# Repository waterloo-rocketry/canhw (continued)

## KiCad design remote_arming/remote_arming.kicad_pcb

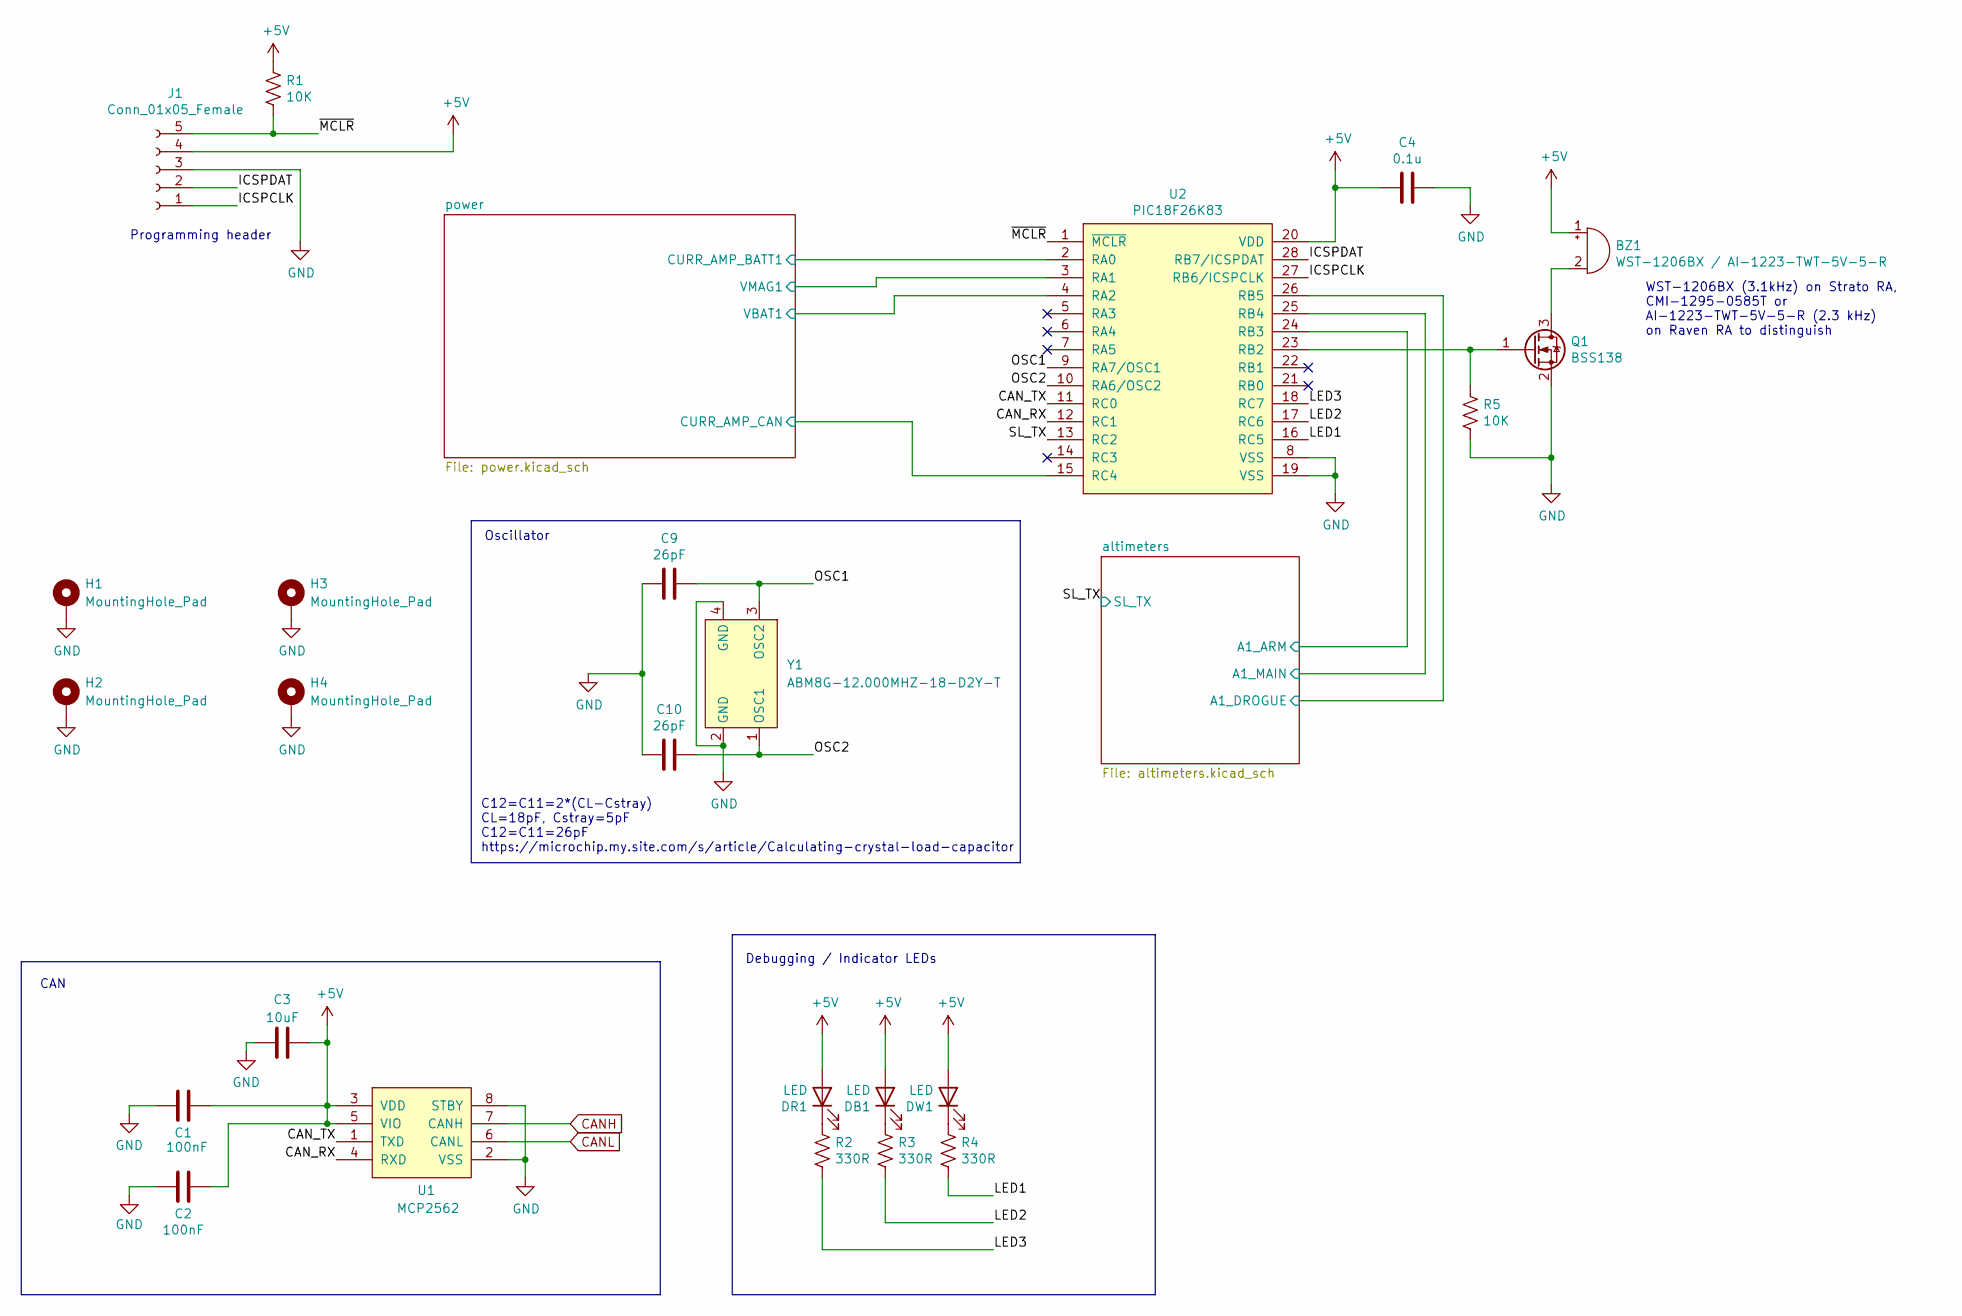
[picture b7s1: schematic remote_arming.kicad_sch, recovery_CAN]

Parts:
BZ1: WST-1206BX / AI-1223-TWT-5V-5-R; Buzzer_12x9.5RM7.6
C1, C2: 100nF; C_0603_1608Metric_Pad1.08x0.95mm_HandSolder
C3: 10uF; C_0603_1608Metric_Pad1.08x0.95mm_HandSolder
C4: 0.1u; C_0603_1608Metric_Pad1.08x0.95mm_HandSolder
C9: 26pF; C_0603_1608Metric
C10: 26pF; C_0603_1608Metric_Pad1.08x0.95mm_HandSolder
DB1: LED; LED_1206_3216Metric_Pad1.42x1.75mm_HandSolder
DR1: LED; LED_1206_3216Metric_Pad1.42x1.75mm_HandSolder
DW1: LED; LED_1206_3216Metric_Pad1.42x1.75mm_HandSolder
H1, H2, H3, H4: MountingHole_Pad; MountingHole_3.2mm_M3_Pad_TopBottom
J1: Conn_01x05_Female; PinSocket_5x2.54_SMD_90deg_952-3198-1-ND
Q1: BSS138; SOT-23_Handsoldering
R1, R5: 10K; R_0603_1608Metric_Pad0.98x0.95mm_HandSolder
R2, R3, R4: 330R; R_0603_1608Metric_Pad0.98x0.95mm_HandSolder
U1: MCP2562; SOIC-8_3.9x4.9mm_P1.27mm
U2: PIC18F26K83; SOIC-28W_7.5x18.7mm_P1.27mm
Y1: ABM8G-12.000MHZ-18-D2Y-T; Crystal_SMD_Abracon_ABM8G-4Pin_3.2x2.5mm

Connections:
+5V: BZ1.1 (-), C1.2, C2.1, C3.2, C4.2, DB1.2 (A), DR1.2 (A), DW1.2 (A), J1.4, R1.1, U1.3 (VDD), U1.5 (VIO), U2.20 (VDD); also elsewhere on the board
/CAN_RX: U1.4 (RXD), U2.12 (RC1)
/CAN_TX: U1.1 (TXD), U2.11 (RC0)
/ICSPCLK: J1.1, U2.27 (RB6/ICSPCLK)
/ICSPDAT: J1.2, U2.28 (RB7/ICSPDAT)
/LED1: R4.2, U2.16 (RC5)
/LED2: R3.2, U2.17 (RC6)
/LED3: R2.2, U2.18 (RC7)
/OSC1: C9.1, U2.9 (RA7/OSC1), Y1.3 (OSC2)
/OSC2: C10.1, U2.10 (RA6/OSC2), Y1.1 (OSC1)
/SL_TX: U2.13 (RC2); also elsewhere on the board
/altimeters/A1_ARM: U2.24 (RB3); also elsewhere on the board
/altimeters/A1_DROGUE: U2.26 (RB5); also elsewhere on the board
/altimeters/A1_MAIN: U2.25 (RB4); also elsewhere on the board
/power/CURR_AMP_BATT1: U2.2 (RA0); also elsewhere on the board
/power/CURR_AMP_CAN: U2.15 (RC4); also elsewhere on the board
/power/VBAT1: U2.4 (RA2); also elsewhere on the board
/power/VMAG1: U2.3 (RA1); also elsewhere on the board
/~MCLR: J1.5, R1.2, U2.1 (~MCLR)
CANH: U1.7 (CANH); also elsewhere on the board
CANL: U1.6 (CANL); also elsewhere on the board
GND: C1.1, C2.2, C3.1, C4.1, C9.2, C10.2, H1.1, H2.1, H3.1, H4.1, J1.3, Q1.2 (S), R5.2, U1.2 (VSS), U1.8 (STBY), U2.8 (VSS), U2.19 (VSS), Y1.2 (GND), Y1.4 (GND); also elsewhere on the board
unnamed: BZ1.2 (+), Q1.3 (D)
unnamed: DB1.1 (K), R3.1
unnamed: DR1.1 (K), R2.1
unnamed: DW1.1 (K), R4.1
unnamed: Q1.1 (G), R5.1, U2.23 (RB2)

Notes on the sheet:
Oscillator
Debugging / Indicator LEDs
WST-1206BX (3.1kHz) on Strato RA, CMI-1295-0585T or AI-1223-TWT-5V-5-R (2.3 kHz) on Raven RA to distinguish
C12=C11=2*(CL-Cstray) CL=18pF, Cstray=5pF C12=C11=26pF https://microchip.my.site.com/s/article/Calculating-crystal-load-capacitor
CAN
Programming header

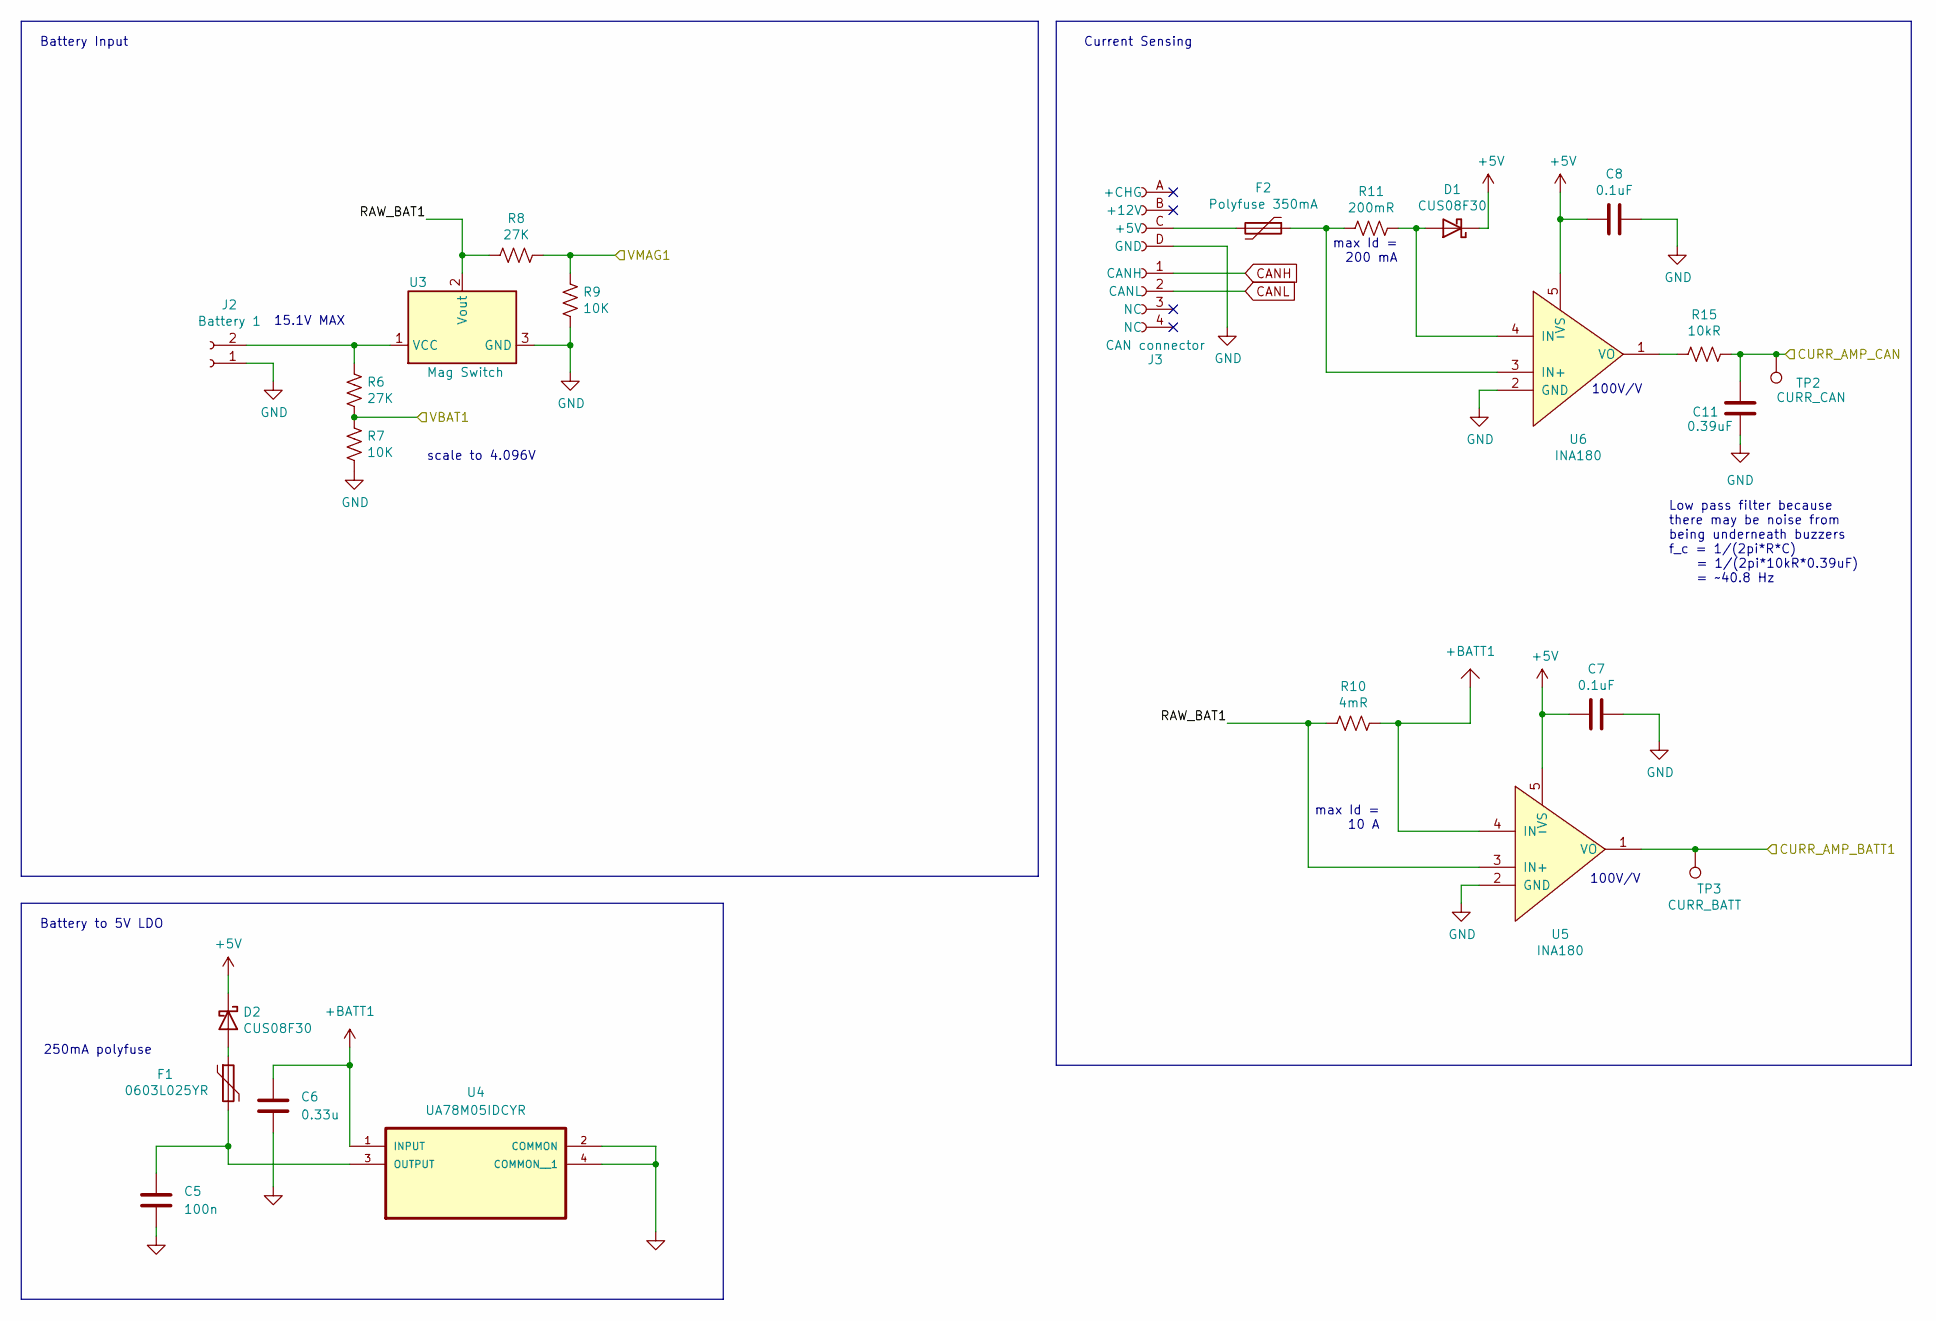
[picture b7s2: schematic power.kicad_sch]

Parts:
C5: 100n; C_0603_1608Metric_Pad1.08x0.95mm_HandSolder
C6: 0.33u; C_0603_1608Metric_Pad1.08x0.95mm_HandSolder
C7, C8: 0.1uF; C_0603_1608Metric_Pad1.08x0.95mm_HandSolder
C11: 0.39uF; C_0603_1608Metric_Pad1.08x0.95mm_HandSolder
D1, D2: CUS08F30; D_SOD-323_HandSoldering
F1: 0603L025YR; Fuse_0603_1608Metric_Pad1.05x0.95mm_HandSolder
F2: Polyfuse 350mA; Fuse_1206_3216Metric_Pad1.42x1.75mm_HandSolder
J2: Battery 1; BarrierBlock_ED2945-ND
J3: CAN connector; connector_Harwin_G125-MH104M4-04AD000P
R6, R8: 27K; R_0603_1608Metric_Pad0.98x0.95mm_HandSolder
R7, R9: 10K; R_0603_1608Metric_Pad0.98x0.95mm_HandSolder
R10: 4mR; R_1206_3216Metric_Pad1.30x1.75mm_HandSolder
R11: 200mR; R_0603_1608Metric_Pad0.98x0.95mm_HandSolder
R15: 10kR; R_0603_1608Metric_Pad0.98x0.95mm_HandSolder
TP2: CURR_CAN; TestPoint_Pad_D2.0mm
TP3: CURR_BATT; TestPoint_Pad_D2.0mm
U3: Mag Switch
U4: UA78M05IDCYR; SOT230P700X180-4N
U5, U6: INA180; SOT-23-5_HandSoldering

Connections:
+5V: C7.2, C8.2, D1.1 (K), D2.1 (K), U5.5 (VS), U6.5 (VS); also elsewhere on the board
+BATT1: C6.1, R10.1, U4.1 (INPUT), U5.4 (IN-); also elsewhere on the board
/power/CURR_AMP_BATT1: TP3.1, U5.1 (VO); also elsewhere on the board
/power/CURR_AMP_CAN: C11.1, R15.2, TP2.1; also elsewhere on the board
/power/RAW_BAT1: R8.2, R10.2, U3.2 (Vout), U5.3 (IN+)
/power/VBAT1: R6.2, R7.1; also elsewhere on the board
/power/VMAG1: R8.1, R9.1; also elsewhere on the board
CANH: J3.1 (CANH); also elsewhere on the board
CANL: J3.2 (CANL); also elsewhere on the board
GND: C5.2, C6.2, C7.1, C8.1, C11.2, J2.1, J3.D (GND), R7.2, R9.2, U3.3 (GND), U4.2 (COMMON), U4.4 (COMMON__1), U5.2 (GND), U6.2 (GND); also elsewhere on the board
unnamed: D1.2 (A), R11.1, U6.4 (IN-)
unnamed: D2.2 (A), F1.1
unnamed: J2.2, R6.1, U3.1 (VCC)
unnamed: F2.2, J3.C (+5V)
unnamed: C5.1, F1.2, U4.3 (OUTPUT)
unnamed: F2.1, R11.2, U6.3 (IN+)
unnamed: R15.1, U6.1 (VO)

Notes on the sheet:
100V/V
max Id = 200 mA
max Id = 10 A
Battery Input
250mA polyfuse
Current Sensing
Battery to 5V LDO
scale to 4.096V
Low pass filter because there may be noise from being underneath buzzers f_c = 1/(2pi*R*C) = 1/(2pi*10kR*0.39uF) = ~40.8 Hz
15.1V MAX

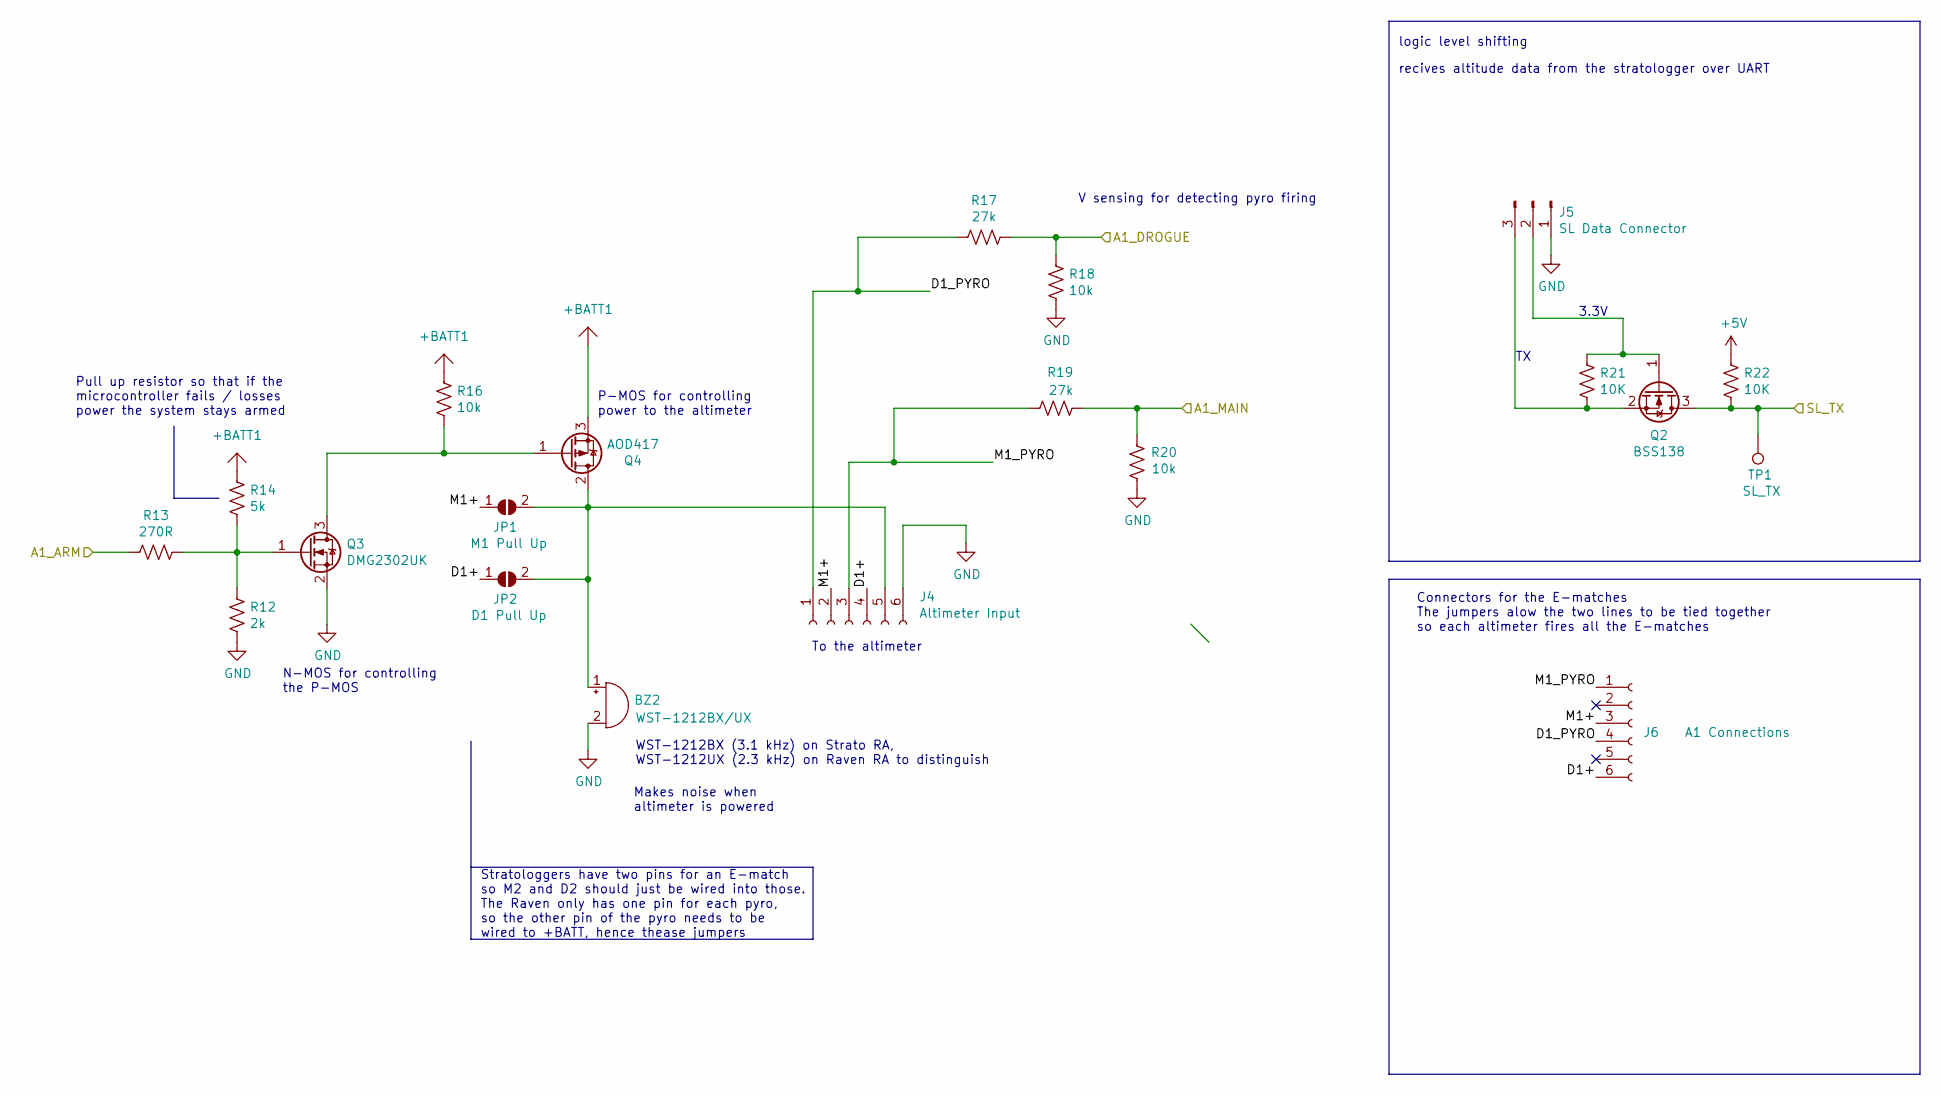
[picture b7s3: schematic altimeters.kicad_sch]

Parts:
BZ2: WST-1212BX/UX; Buzzer_12x9.5RM7.6
J4: Altimeter Input; connector_Harwin_G125–MG10605M4P
J5: SL Data Connector; JST_EH_S3B-EH_1x03_P2.50mm_Horizontal
J6: A1 Connections; connector_Harwin_G125–MG10605M4P
JP1: M1 Pull Up; SolderJumper-2_P1.3mm_Open_RoundedPad1.0x1.5mm
JP2: D1 Pull Up; SolderJumper-2_P1.3mm_Open_RoundedPad1.0x1.5mm
Q2: BSS138; SOT-23_Handsoldering
Q3: DMG2302UK; SOT-23_Handsoldering
Q4: AOD417; TO-252-2
R12: 2k; R_0603_1608Metric_Pad0.98x0.95mm_HandSolder
R13: 270R; R_0603_1608Metric_Pad0.98x0.95mm_HandSolder
R14: 5k; R_0603_1608Metric_Pad0.98x0.95mm_HandSolder
R16, R18, R20: 10k; R_0603_1608Metric_Pad0.98x0.95mm_HandSolder
R17, R19: 27k; R_0603_1608Metric_Pad0.98x0.95mm_HandSolder
R21, R22: 10K; R_0603_1608Metric_Pad0.98x0.95mm_HandSolder
TP1: SL_TX; TestPoint_Pad_D2.0mm

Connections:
+5V: R22.1; also elsewhere on the board
+BATT1: Q4.3 (S), R14.1, R16.1; also elsewhere on the board
/SL_TX: Q2.3 (D), R22.2, TP1.1; also elsewhere on the board
/altimeters/A1_ARM: R13.2; also elsewhere on the board
/altimeters/A1_DROGUE: R17.1, R18.2; also elsewhere on the board
/altimeters/A1_MAIN: R19.2, R20.2; also elsewhere on the board
/altimeters/D1+: J4.4, J6.6, JP2.1 (A)
/altimeters/D1_PYRO: J4.1, J6.4, R17.2
/altimeters/M1+: J4.2, J6.3, JP1.1 (A)
/altimeters/M1_PYRO: J4.3, J6.1, R19.1
GND: BZ2.2 (+), J4.6, J5.1, Q3.2 (S), R12.2, R18.1, R20.1; also elsewhere on the board
unnamed: BZ2.1 (-), J4.5, JP1.2 (B), JP2.2 (B), Q4.2 (D)
unnamed: J5.2, Q2.1 (G), R21.1
unnamed: J5.3, Q2.2 (S), R21.2
unnamed: Q3.3 (D), Q4.1 (G), R16.2
unnamed: Q3.1 (G), R12.1, R13.1, R14.2

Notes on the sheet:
To the altimeter
N-MOS for controlling the P-MOS
logic level shifting
WST-1212BX (3.1 kHz) on Strato RA, WST-1212UX (2.3 kHz) on Raven RA to distinguish
P-MOS for controlling power to the altimeter
3.3V
recives altitude data from the stratologger over UART
Pull up resistor so that if the microcontroller fails / losses power the system stays armed
Stratologgers have two pins for an E-match so M2 and D2 should just be wired into those. The Raven only has one pin for each pyro, so the other pin of the pyro needs to be wired to +BATT, hence thease jumpers
V sensing for detecting pyro firing
Connectors for the E-matches The jumpers alow the two lines to be tied together so each altimeter fires all the E-matches
Makes noise when altimeter is powered

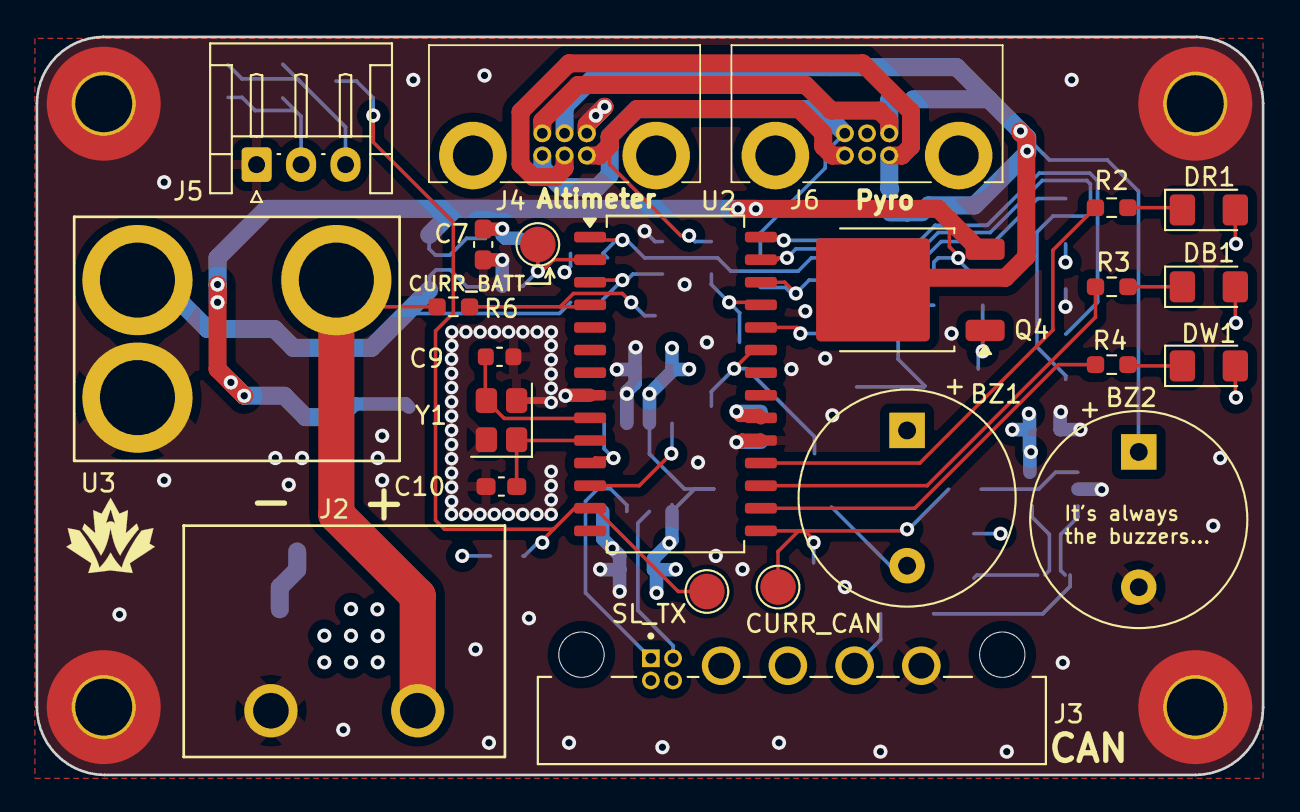
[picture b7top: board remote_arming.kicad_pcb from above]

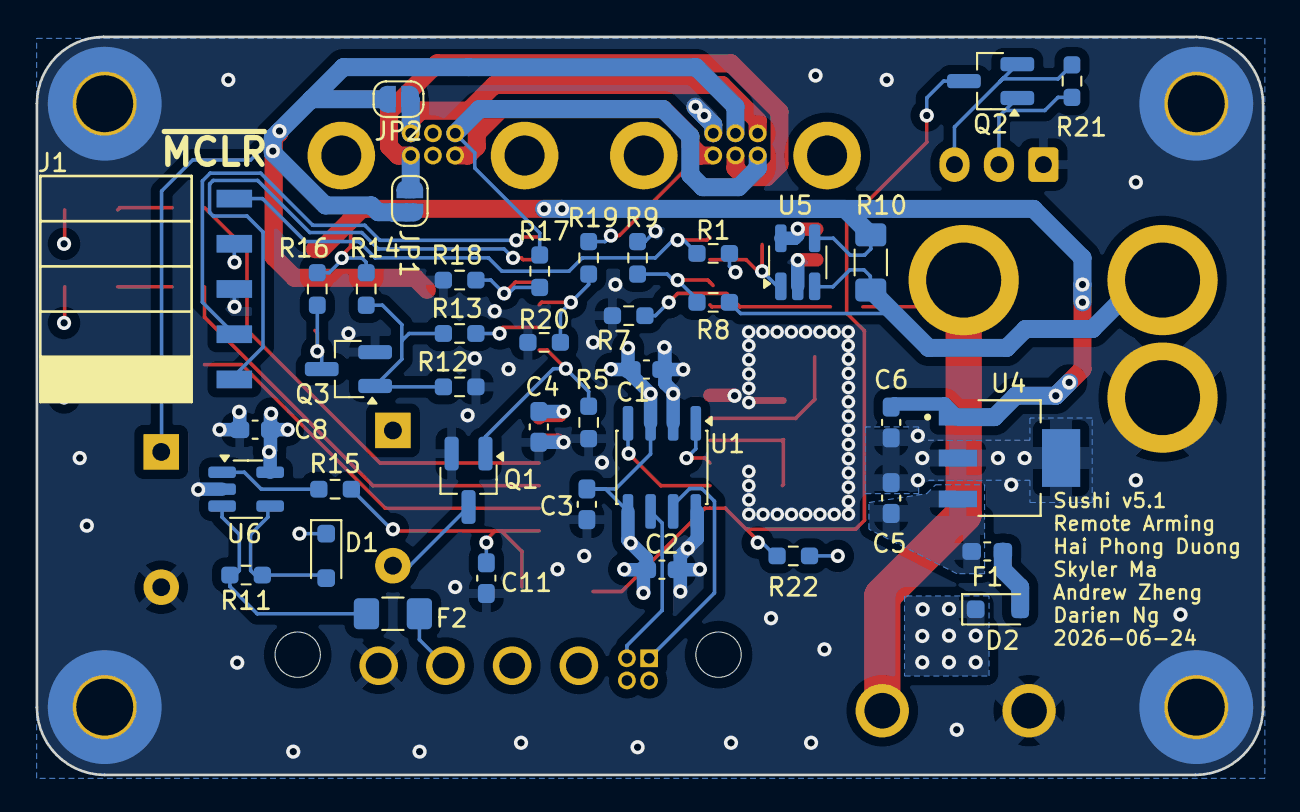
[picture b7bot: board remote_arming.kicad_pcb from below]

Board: 4 copper layers, 68.9 x 41.5 mm, 68 parts (40 on the bottom side), 45 nets.

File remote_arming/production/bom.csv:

Designator,Footprint,Quantity,Value,LCSC Part #
BZ1,Buzzer_12x9.5RM7.6,1,CMI-1295-0585T,
BZ2,Buzzer_12x9.5RM7.6,1,CMI-1295-1285T,
"C1, C2",0603,2,100nF,
"C10, C9",0603,2,26pF,
C11,0603,1,0.39uF,
C3,0603,1,10uF,
C4,0603,1,0.1u,
C5,0603,1,100n,
C6,0603,1,0.33u,
"C7, C8",0603,2,0.1uF,
"D1, D2",D_SOD-323_HandSoldering,2,CUS08F30,
"DB1, DR1, DW1",1206,3,LED,
F1,0603,1,0603L025YR,
F2,1206,1,Polyfuse 350mA,
J1,PinSocket_5x2.54_SMD_90deg_952-3198-1-ND,1,Conn_01x05_Female,
J2,BarrierBlock_ED2945-ND,1,Battery 1,
J3,connector_Harwin_G125-MH104M4-04AD000P,1,CAN connector,
J4,connector_Harwin_G125–MG10605M4P,1,Altimeter Input,
J5,JST_EH_S3B-EH_1x03_P2.50mm_Horizontal,1,SL Data Connector,
J6,connector_Harwin_G125–MG10605M4P,1,A1 Connections,
JP1,SolderJumper-2_P1.3mm_Open_RoundedPad1.0x1.5mm,1,M1 Pull Up,
JP2,SolderJumper-2_P1.3mm_Open_RoundedPad1.0x1.5mm,1,D1 Pull Up,
"Q1, Q2",SOT-23_Handsoldering,2,BSS138,
Q3,SOT-23_Handsoldering,1,DMG2302UK,
Q4,TO-252-2,1,AOD417,
"R1, R16, R18, R20, R21, R22, R5, R7, R9",0603,9,10K,
R10,1206,1,4mR,
R11,0603,1,200mR,
R12,0603,1,2k,
R13,0603,1,270R,
R14,0603,1,5k,
R15,0603,1,10kR,
"R17, R19, R6, R8",0603,4,27k,
"R2, R3, R4",0603,3,330R,
TP1,TestPoint_Pad_D2.0mm,1,SL_TX,
TP2,TestPoint_Pad_D2.0mm,1,CURR_CAN,
TP3,TestPoint_Pad_D2.0mm,1,CURR_BATT,
U1,SOIC-8_3.9x4.9mm_P1.27mm,1,MCP2562,
U2,SOIC-28W_7.5x18.7mm_P1.27mm,1,PIC18F26K83,
U3,Mag Switch,1,Mag Switch,
U4,SOT230P700X180-4N,1,UA78M05IDCYR,
"U5, U6",SOT-23-5_HandSoldering,2,INA180,
Y1,Crystal_SMD_Abracon_ABM8G-4Pin_3.2x2.5mm,1,ABM8G-12.000MHZ-18-D2Y-T,

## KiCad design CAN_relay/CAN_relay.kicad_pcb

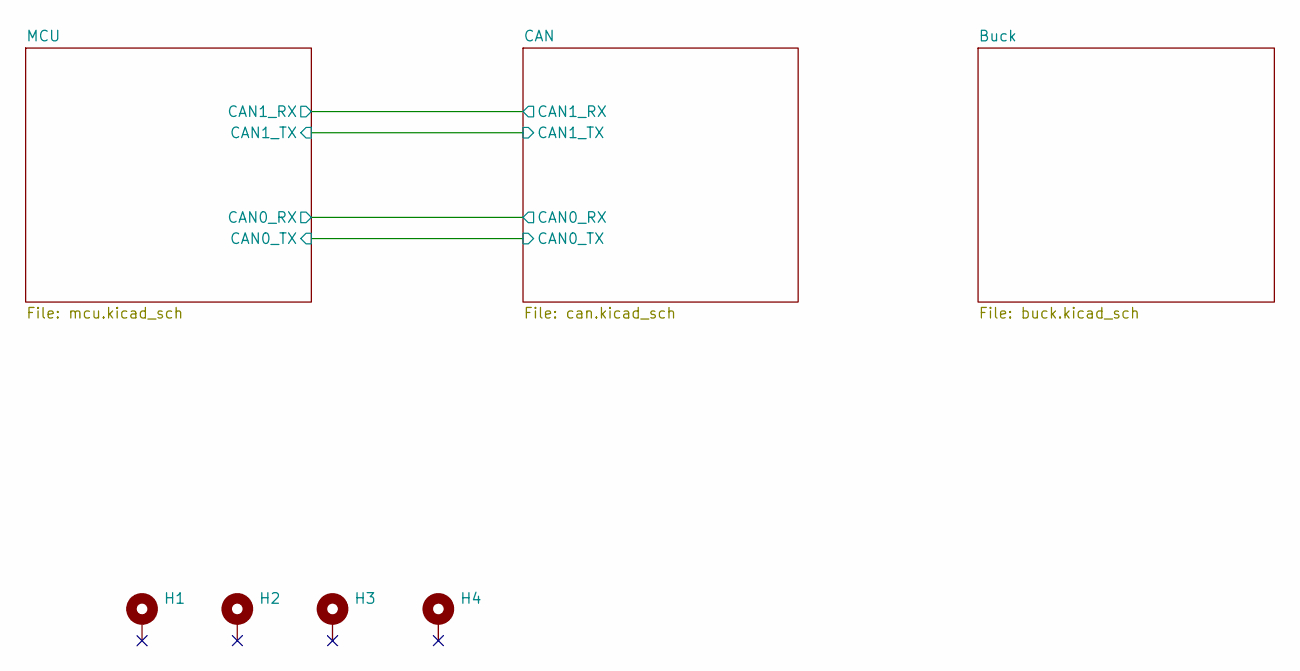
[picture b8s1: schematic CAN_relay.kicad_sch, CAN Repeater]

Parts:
H1, H2, H3, H4: MountingHole_Pad; MountingHole_3.2mm_M3_Pad

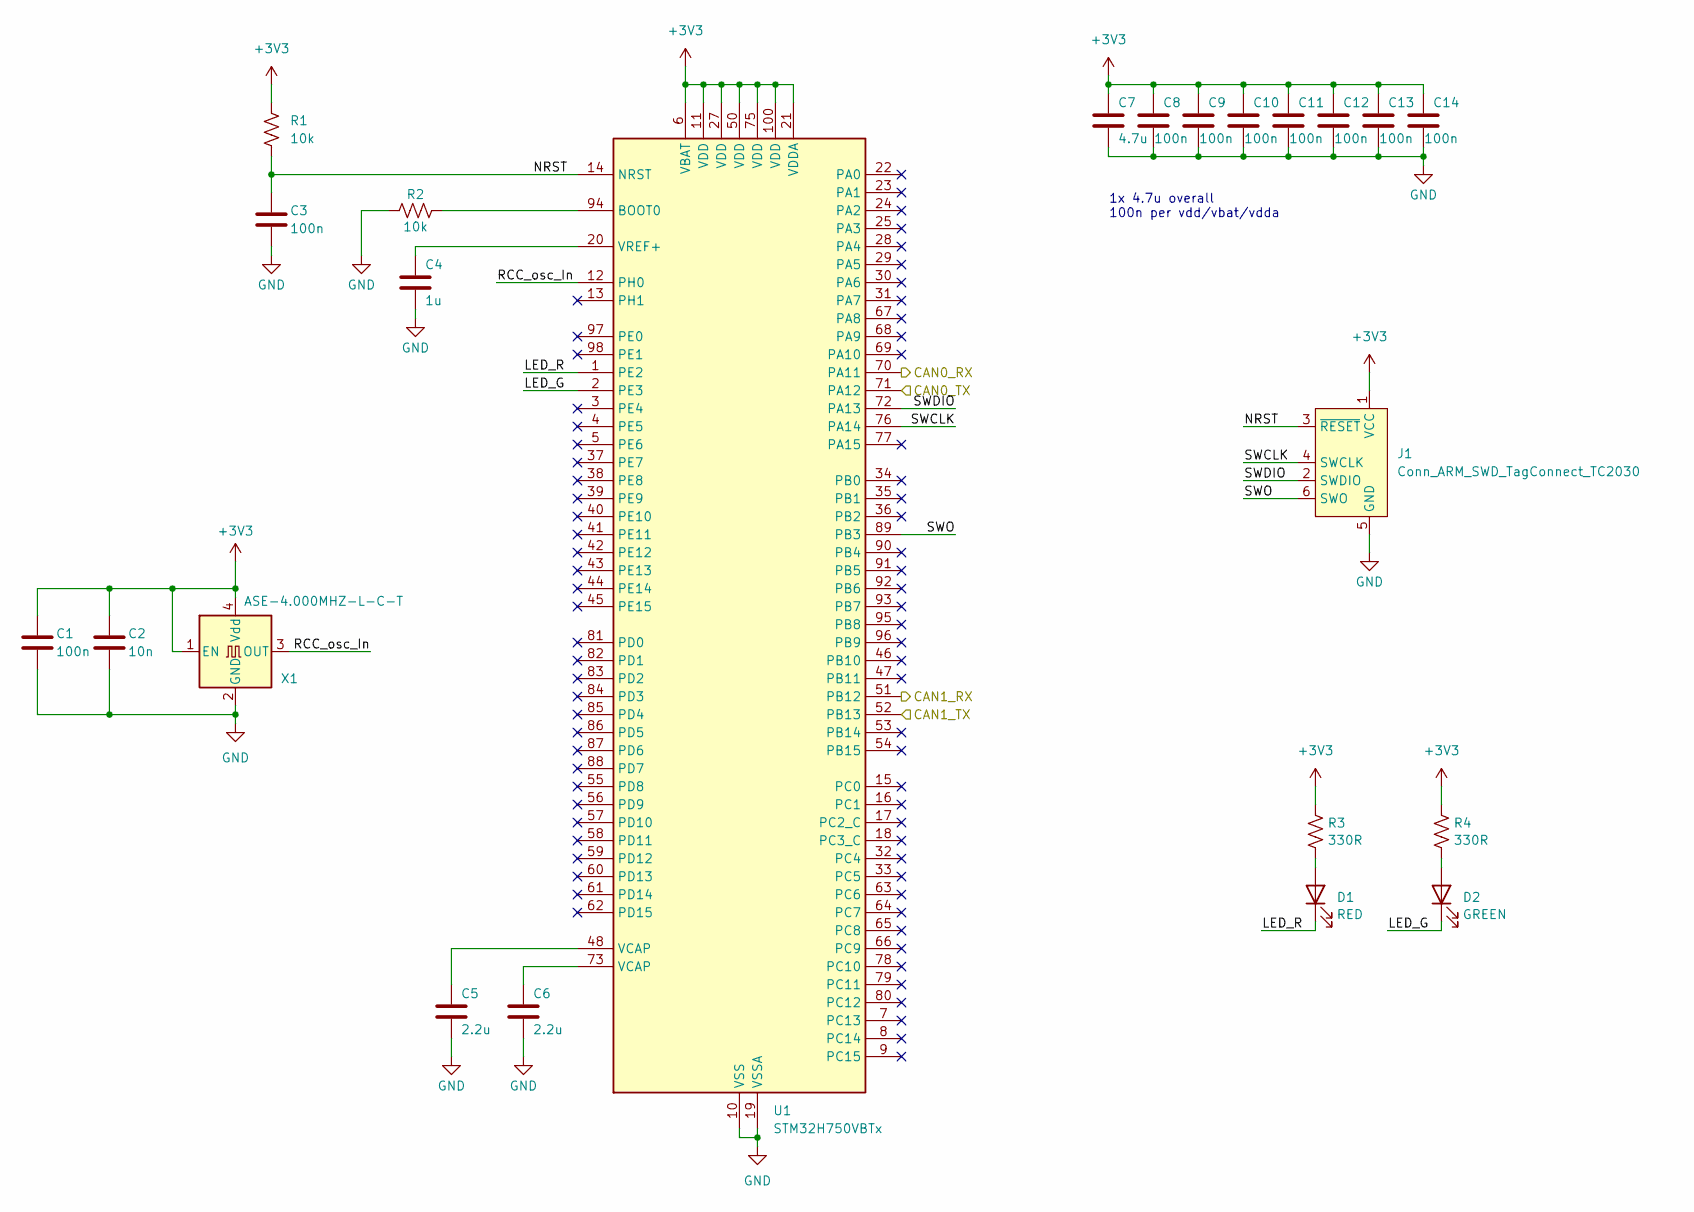
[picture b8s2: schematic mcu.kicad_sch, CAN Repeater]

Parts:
C1, C3, C8, C9, C10, C11, C12, C13, C14: 100n; C_0603_1608Metric_Pad1.08x0.95mm_HandSolder
C2: 10n; C_0603_1608Metric_Pad1.08x0.95mm_HandSolder
C4: 1u; C_0603_1608Metric_Pad1.08x0.95mm_HandSolder
C5, C6: 2.2u; C_0603_1608Metric_Pad1.08x0.95mm_HandSolder
C7: 4.7u; C_0603_1608Metric_Pad1.08x0.95mm_HandSolder
D1: RED; LED_1206_3216Metric_Pad1.42x1.75mm_HandSolder
D2: GREEN; LED_1206_3216Metric_Pad1.42x1.75mm_HandSolder
J1: Conn_ARM_SWD_TagConnect_TC2030; Tag-Connect_TC2030-IDC-FP_2x03_P1.27mm_Vertical
R1, R2: 10k; R_0603_1608Metric_Pad0.98x0.95mm_HandSolder
R3, R4: 330R; R_0603_1608Metric_Pad0.98x0.95mm_HandSolder
U1: STM32H750VBTx; LQFP-100_14x14mm_P0.5mm
X1: ASE-4.000MHZ-L-C-T; Oscillator_SMD_Abracon_ASE-4Pin_3.2x2.5mm; LCSC Part # C437121

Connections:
+3V3: C1.1, C2.1, C7.1, C8.1, C9.1, C10.1, C11.1, C12.1, C13.1, C14.1, J1.1 (VCC), R1.1, R3.1, R4.1, U1.6 (VBAT), U1.11 (VDD), U1.21 (VDDA), U1.27 (VDD), U1.50 (VDD), U1.75 (VDD), U1.100 (VDD), X1.1 (EN), X1.4 (Vdd); also elsewhere on the board
/CAN/CAN0_RX: U1.70 (PA11); also elsewhere on the board
/CAN/CAN0_TX: U1.71 (PA12); also elsewhere on the board
/CAN/CAN1_RX: U1.51 (PB12); also elsewhere on the board
/CAN/CAN1_TX: U1.52 (PB13); also elsewhere on the board
/MCU/LED_G: D2.1 (K), U1.2 (PE3)
/MCU/LED_R: D1.1 (K), U1.1 (PE2)
/MCU/NRST: C3.1, J1.3 (~RESET), R1.2, U1.14 (NRST)
/MCU/RCC_osc_In: U1.12 (PH0), X1.3 (OUT)
/MCU/SWCLK: J1.4 (SWCLK), U1.76 (PA14)
/MCU/SWDIO: J1.2 (SWDIO), U1.72 (PA13)
/MCU/SWO: J1.6 (SWO), U1.89 (PB3)
GND: C1.2, C2.2, C3.2, C4.2, C5.2, C6.2, C7.2, C8.2, C9.2, C10.2, C11.2, C12.2, C13.2, C14.2, J1.5 (GND), R2.1, U1.10 (VSS), U1.19 (VSSA), U1.26 (VSS), U1.49 (VSS), U1.74 (VSS), U1.99 (VSS), X1.2 (GND); also elsewhere on the board
unnamed: C5.1, U1.48 (VCAP)
unnamed: C6.1, U1.73 (VCAP)
unnamed: D1.2 (A), R3.2
unnamed: D2.2 (A), R4.2
unnamed: R2.2, U1.94 (BOOT0)
unnamed: C4.1, U1.20 (VREF+)

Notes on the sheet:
1x 4.7u overall 100n per vdd/vbat/vdda

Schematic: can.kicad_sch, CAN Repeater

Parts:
C16, C17, C18, C19: 100n; C_0603_1608Metric_Pad1.08x0.95mm_HandSolder
D3, D4: PMEG2010ER; Nexperia_CFP3_SOD-123W
D5, D6: ESDCAN01-2BLY; SOT-23; LCSC Part # C1976606
F1: PTC 250mA; Fuse_1206_3216Metric_Pad1.42x1.75mm_HandSolder
J2, J3: G125-MH104M4-04AD000P; connector_Harwin_G125-MH104M4-04AD000P
JP1, JP2: SolderJumper_2_Open; SolderJumper-2_P1.3mm_Open_RoundedPad1.0x1.5mm
R5, R6: 120R; R_0603_1608Metric_Pad0.98x0.95mm_HandSolder; not fitted
TP1, TP3: RCAN_TX; TestPoint_Pad_D1.0mm
TP2, TP4: RCAN_RX; TestPoint_Pad_D1.0mm
U2, U3: TCAN3413DDFR; Manufacturer_Part_Number TCAN3413DDFR

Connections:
+3V3: C16.1, C17.1, C18.1, C19.1, U2.3 (VCC), U2.5 (VIO), U3.3 (VCC), U3.5 (VIO); also elsewhere on the board
+VIN: F1.2; also elsewhere on the board
/CAN/CAN0_H: D6.1 (K), J2.1 (CANH), JP1.2 (B), R6.2, U3.7 (CANH)
/CAN/CAN0_L: D6.2 (K), J2.2 (CANL), JP2.2 (B), R6.1, U3.6 (CANL)
/CAN/CAN0_RX: TP4.1 (1_1), U3.4 (RXD); also elsewhere on the board
/CAN/CAN0_TX: TP3.1 (1_1), U3.1 (TXD); also elsewhere on the board
/CAN/CAN1_H: D5.1 (K), J3.1 (CANH), JP1.1 (A), R5.2, U2.7 (CANH)
/CAN/CAN1_L: D5.2 (K), J3.2 (CANL), JP2.1 (A), R5.1, U2.6 (CANL)
/CAN/CAN1_RX: TP2.1 (1_1), U2.4 (RXD); also elsewhere on the board
/CAN/CAN1_TX: TP1.1 (1_1), U2.1 (TXD); also elsewhere on the board
GND: C16.2, C17.2, C18.2, C19.2, D5.3 (A), D6.3 (A), J2.D (GND), J3.D (GND), U2.2 (GND), U3.2 (GND); also elsewhere on the board
unnamed: D3.2 (A), J2.B (+12V), J3.B (+12V)
unnamed: D3.1 (K), D4.1 (K), F1.1
unnamed: D4.2 (A), J2.C (+5V), J3.C (+5V)
unnamed: J2.A (+CHG), J3.A (+CHG)

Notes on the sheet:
Power passthrough

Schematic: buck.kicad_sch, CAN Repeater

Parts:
C20, C23, C24: 22u; C_0805_2012Metric_Pad1.18x1.45mm_HandSolder
C21: 100n; C_0603_1608Metric_Pad1.08x0.95mm_HandSolder
C22: 1u; C_0603_1608Metric_Pad1.08x0.95mm_HandSolder
U4: TPSM33606S3QRDNRQ1

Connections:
+3V3: C23.1, C24.1, U4.4 (VOUT), U4.9 (FB); also elsewhere on the board
+VIN: C20.1, C21.1, U4.2 (EN), U4.3 (VIN); also elsewhere on the board
GND: C20.2, C21.2, C22.2, C23.2, C24.2, U4.10 (GND), U4.11 (MODE/SYNCH); also elsewhere on the board
unnamed: C22.1, U4.8 (VCC)

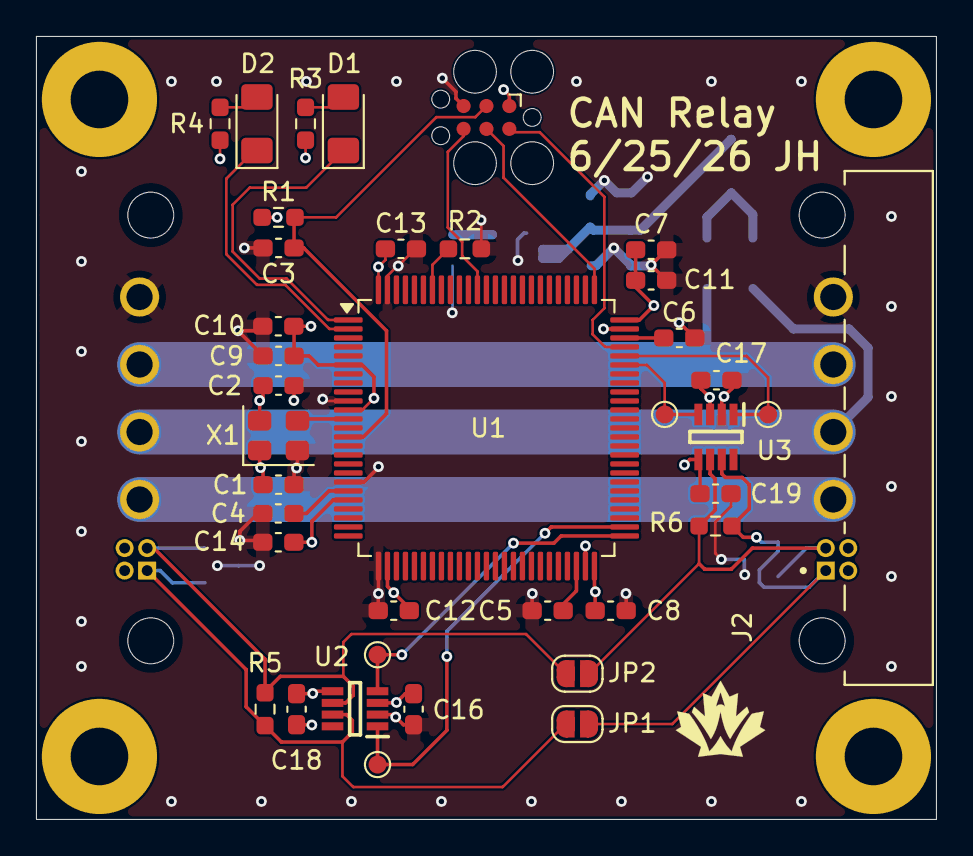
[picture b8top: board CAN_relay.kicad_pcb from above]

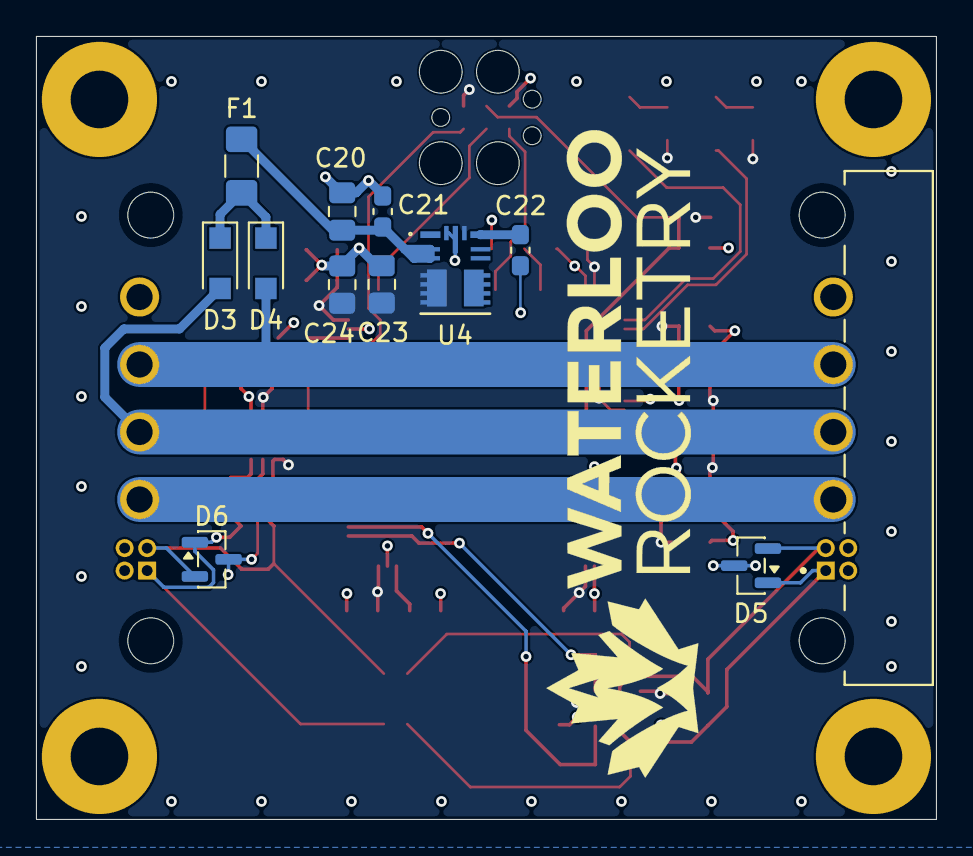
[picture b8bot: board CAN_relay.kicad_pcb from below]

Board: 4 copper layers, 50.0 x 43.5 mm, 54 parts (12 on the bottom side), 29 nets.

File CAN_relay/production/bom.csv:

Designator,Footprint,Quantity,Value,LCSC Part #
"C1, C10, C11, C12, C13, C14, C16, C17, C18, C19, C21, C3, C8, C9",0603,14,100n,
C2,0603,1,10n,
"C20, C23, C24",0805,3,22u,
"C22, C4",0603,2,1u,
"C5, C6",0603,2,2.2u,
C7,0603,1,4.7u,
D1,1206,1,RED,
D2,1206,1,GREEN,
"D3, D4",Nexperia_CFP3_SOD-123W,2,PMEG2010ER,
"D5, D6",SOT-23,2,ESDCAN01-2BLY,C1976606
F1,1206,1,PTC 250mA,
"J2, J3",connector_Harwin_G125-MH104M4-04AD000P,2,G125-MH104M4-04AD000P,
"R1, R2",0603,2,10k,
"R3, R4",0603,2,330R,
"R5, R6",0603,2,120R,
U1,LQFP-100_14x14mm_P0.5mm,1,STM32H750VBTx,
"U2, U3",TCAN3413DDFR,2,TCAN3413DDFR,
U4,TPSM33606S3QRDNRQ1,1,TPSM33606S3QRDNRQ1,
X1,Oscillator_SMD_Abracon_ASE-4Pin_3.2x2.5mm,1,ASE-4.000MHZ-L-C-T,C437121
